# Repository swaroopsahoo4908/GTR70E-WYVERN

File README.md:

# GTR70E WYVERN — fin-controlled research rocket

Authors: Swaroop Sahoo, Chris Liu, Allison Hong

A single-stage, 58 mm, actively stabilised rocket. Four servo-driven triangular fins sit in one ring just above the motor, all at the same station, and steer it on ascent; four fixed rectangular stabilizers run the length of the motor and keep it passively stable. The motor's ejection gas reaches the recovery bay through a printed PC-FR tube on the centreline, and the avionics ride on a square spine around that tube. The flight computer is a Raspberry Pi Pico 2 W (radio left off) that logs everything to an Adafruit 4682 microSD; there is no radio, and a pushbutton through the wall arms it on the pad. The thrust-vector-control revision lives, complete, in `TVC ARCHIVED/`.

## Key numbers (`Documentation/CANONICAL_NUMBERS.md` is the full, generated list)

| | |
|---|---|
| Length / OD | 693 mm / 58 mm, four printed sections (each fits a 256 mm printer), only the nose separates |
| Liftoff mass | 784.5 g on an AeroTech Econojet F42-4T (T/W 4.7 avg; 4 motors $98.98 at eRockets, no certification) |
| CG / CP / margin | 338 / 422 mm, 1.44 cal at liftoff, 1.63 at burnout; 253 g nose ballast, stabilizers 81 x 20 mm at 45°, H45 flight fins |
| Rail exit | 15.0 m/s off the 6 ft Estes Pro Series II rail (printed 1010 buttons) |
| Apogee | 176 m (577 ft, under the 600 ft cap) at 6.3 s; motor ejection (4 s delay) via the central printed PC-FR bypass tube |
| Control | 4 x EMAX ES9251 II in one ring on their own 5 V rail (rev 3f; was the KST X08 Plus), bases 5 mm from the axis, ±15°, q-scheduled PID at 200 Hz; gust case 0.6° RMS tilt vs 10.8° with fins locked; fins active from rail exit until q̄ < 15 Pa (96 % of the ascent); in-flight authority manoeuvre (doublets + 1° steps) |
| Avionics | Raspberry Pi Pico 2 W (rev 4b, radio off) logging to an Adafruit 4682 microSD; BNO085 on one I2C bus, BMP388 + BME688 on the other, on a square spine around the bypass tube; arm button + LED in the -Y wall |
| Power | 2S 450 mAh through a Pololu 2810 MOSFET switch flipped through a wall slot; 26-min mission uses 35 mAh (6.9x margin) |
| Data | 96 B records at 100 Hz to the card once armed, manoeuvre summary in `MANxxx.TXT`; USB CSV at 10 Hz on the bench and pad only; no telemetry in flight |

## Research questions (`Documentation/Research_Plan.md`)

Main question: how do aerofoil section (flat plate, 6 % double wedge, NACA 0006, NACA 0012) and fin height (20-40 mm) set the control authority of a servo-actuated triangular fin, and which combination gives the most? Tunnel Phase A (one fin on a reflection plane) plus simulation.

- SQ1: how much do the rectangular stabilizers reduce installed authority, as a function of span and azimuth? `wf_stabilizer.py` plus tunnel Phase B (full finset, stabilizers off / 30 / 40 mm).
- SQ2: how well do the simulations predict the tunnel, and how far does that carry to flight? Three launches of the best section at H* - 5, H*, H* + 5.

## Repository

```
GTR70E WYVERN/
├── README.md
├── Documentation/
│   ├── Design_Overview.md          architecture, servo ring, spine, stability/ballast, motor, bypass sizing
│   ├── Research_Plan.md            main RQ + SQ1/SQ2, single fin vs four, test matrix, selection rule
│   ├── Wind_Tunnel_Adaptation.md   Phase A half-model (stock section), Phase B 200 x 200 x 750 + stabilizer tail
│   ├── Electronics_Telemetry.md    board choice, pin map, power + battery budget, arming, logging, firmware
│   ├── Build_and_Test.md           print settings, assembly stages, sign check, ejection test, pad procedure
│   ├── Decisions_and_Risks.md      decision log + risk register
│   ├── CANONICAL_NUMBERS.md        generated by gen_canonical_md.py
│   ├── WYVERN_BOM.xlsx             built by build_bom.py: one sheet, Rocket / Wind Tunnel / Flow-Vis, everything to buy
│   └── diagrams/                   D0 renders, D1 layout, D2 sections, D3 assembly, D4 tunnel, D5 research plan, D6 fit check
├── 3D parts/
│   ├── _generator/                 gen_wyvern_fin.py (CadQuery), gen_fit_assembly.py (fit check), mass_report.json
│   ├── vendor/                     Adafruit + Pololu STEP models of the bought boards
│   ├── flight/                     STEP + STL for every printed flight part
│   ├── control_fins/<profile>/     4 profiles x H20-45
│   ├── wind_tunnel/                WTA_* Phase A panel/cradle/transition, WTB_* stabilizer tail + blades, WT_* Phase B
│   └── assembly/                   full assembly STEP + STL, fit-check assembly + FIT_REPORT.md
├── Simulations/
│   ├── wf_core.py                  single source of truth (geometry, masses, motors, aero, spine board layout)
│   ├── motors/                     RASP .eng curves from thrustcurve.org (F67W, F67C, G74W, F50T, G40W)
│   ├── wf_flightsim.py             3-DOF closed-loop flight sim + motor trade + gain tuning + authority manoeuvre
│   ├── wf_fin_authority.py         4 x 8 profile/height authority sweep (main RQ)
│   ├── wf_stabilizer.py            stabilizer span x azimuth sweep (SQ1)
│   ├── wf_stabilizer_planform_trade.py  equal-span / AIM-54 layout trade (S4 plot)
│   ├── wf_apogee_cap_trade.py      rev 3d: 600 ft cap without losing authority (C plot)
│   ├── wf_motor_study.py           F42-4T vs F27R-4 / F20W-4 / F20W-7 on 6-10 ft rails (D plot)
│   ├── wf_bypass.py · wf_power.py
│   ├── wyvern_finsim/              GUI simulation & dataset suite (run_gui.py), headless datagen.py
│   └── CFD/                        vortex-panel 2D + vlm.py 3D vortex lattice + simscale/ RANS package (10 cases)
├── Flight Computer/
│   ├── firmware/wyvern_fin/        flight firmware (Pico 2 W, arduino-pico, compiles) + sil_host/
│   ├── host/                       wyvern_host.py: SD log decoder, USB live plot
│   ├── test_code/                  t1 I2C scan, t2 servo cal + bench sign check, t3 arm button + SD soak
│   └── wiring/                     gen_wiring.py -> W1 wiring, W2 power tree, W3 system, W4 spine + perfboard
├── Wind Tunnel/                    Jerrod H STLs (unchanged) + wt_balance_daq (Metro M4: servo + 2 x HX711 balance + BME688)
├── Data/                           Flight / Motor / Wind Tunnel (empty until testing)
├── Paper/
└── TVC ARCHIVED/                   everything from the TVC revision that is not reused
```

## Re-running the cascade

```bash
pip install cadquery numpy-stl matplotlib openpyxl
cd "3D parts/_generator" && python3 gen_wyvern_fin.py          # CAD + mass_report.json (~25 s)
python3 gen_fit_assembly.py                                     # fit check with vendor models (~2 min)
cd ../../Simulations
python3 wf_core.py --report                                    # canonical_numbers.json
python3 CFD/run_airfoil_cfd.py && python3 CFD/vlm.py
python3 wf_flightsim.py            # add --retune after any mass/geometry change
python3 wf_fin_authority.py        # ~1 min
python3 wf_stabilizer.py           # ~20 s
python3 wf_stabilizer_planform_trade.py
python3 wf_apogee_cap_trade.py && python3 wf_motor_study.py
python3 wf_bypass.py && python3 wf_power.py
cd ../Documentation && python3 gen_canonical_md.py && python3 build_bom.py
cd diagrams && python3 gen_vehicle_drawings.py && python3 gen_cad_renders.py && python3 gen_tunnel_research.py && python3 gen_fit_render.py
cd "../../Flight Computer/wiring" && python3 gen_wiring.py
```

Then re-run `python3 "Flight Computer/firmware/sil_host/sil_check.py"` (firmware vs sim manoeuvre metrics) and `python3 Simulations/CFD/simscale/gen_simscale.py` if the geometry changed. Copy any changed gains or limits into `Flight Computer/firmware/wyvern_fin/fc_config.h` and run `python3 sync_headers.py`.

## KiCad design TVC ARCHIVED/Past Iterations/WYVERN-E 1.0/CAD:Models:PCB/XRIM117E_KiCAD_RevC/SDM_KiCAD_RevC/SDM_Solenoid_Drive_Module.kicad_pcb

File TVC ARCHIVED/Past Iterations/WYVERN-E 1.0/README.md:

# WYVERN-E 1.0

An experimental 70/127 mm research rocket demonstrating jet-vane thrust-vector control and a
custom avionics stack, serving as the first hardware PDR for the XRIM-117 WYVERN concept.

A Skylight Rocketry venture. Architecture revision PDR-004. *Superseded by WYVERN-E 2.0
(open-source solenoid TVC + custom RP2350B two-board PCB).*

---

## Overview

WYVERN-E 1.0 established the physical design envelope — two body diameter candidates (70 mm PDR-002
and 127 mm PDR-003/004), a jet-vane TVC geometry, the wind tunnel test infrastructure, and the
first KiCad avionics layout (XRIM117 RevB/C and XRIM117E). The program reached PDR-004 full
assembly before being superseded by the cleaner open-source two-board architecture of 2.0.

---

## Folder structure

```
WYVERN-E 1.0/
├── README.md                          ← this file
├── CAD:Models:PCB/                    ← OpenRocket sims, STL parts, KiCad PCBs, SVG schematics
│   ├── XRIM117_PTD_PDR002_70mm.ork    ← 70 mm PDR-002 baseline sim
│   ├── XRIM117E_PDR003_127mm.ork      ← 127 mm PDR-003 sim
│   ├── XRIM117E_PDR003_127mm_F15.ork  ← 127 mm F15-motor variant
│   ├── XRIM117E_PDR003_127mm_FLIGHT.ork
│   ├── XRIM117E_PDR004_FULL.ork       ← PDR-004 full assembly sim
│   ├── XRIM117E_PDR004_TVC_ONLY.ork   ← PDR-004 TVC-only stage sim
│   ├── XRIM117_all_parts/             ← 19-part STL library (nose, tubes, fins, gimbal, motor mount…)
│   ├── XRIM117E_KiCAD_RevC/           ← XRIM117E avionics KiCad RevC
│   ├── XRIM117_KiCAD_RevB/            ← XRIM117 avionics KiCad RevB
│   ├── XRIM117_EasyEDA_v3/            ← EasyEDA schematic source (pre-KiCad migration)
│   ├── xrim117_avionics_v4.svg        ← avionics schematic (SVG)
│   ├── xrim117_jetavane_tvc.svg       ← jet-vane TVC diagram (SVG)
│   ├── XRIM117_PCB_Layouts.html       ← rendered PCB layout view
│   ├── WYVERN_Engineering_Analysis.pdf ← structural and aero analysis
│   └── WYVERN_Simulator.md            ← flight simulation environment notes
├── Wind Tunnel/                       ← wind tunnel design, BOM, and test data
│   ├── Wind Tunnel Build.md           ← construction and instrumentation notes
│   ├── wind_tunnel_bom.xlsx           ← wind tunnel bill of materials
│   ├── WYVERN_wind_tunnel_spec.html   ← tunnel specification (HTML)
│   ├── WindTunnel_all_parts/          ← 14-part STL assembly (bellmouth, settling chamber,
│   │                                     contraction cone ×6, test section ×3, diffuser, fan)
│   └── WYVERN_WindTunnel_v2.zip       ← full tunnel archive
├── Docs:Decks/                        ← presentations and technical overview documents
│   ├── XRIM117_WYVERN_PitchDeck.pptx ← investor/competition pitch deck
│   ├── XRIM117_WYVERN_TechOverview.docx ← technical overview document
│   ├── XRIM117_PTD_PDR002_RevA_70mm.docx ← PDR-002 preliminary design review
│   └── XRIM117_NDA.docx               ← NDA (superseded by WYVERN/WYVERN NDA.md)
└── _OLD FILES/                        ← superseded PCB revisions (kept for reference)
    └── PCB/FCM_KiCAD/                 ← earlier KiCad layout with gerbers
```

---

## Key design parameters (PDR-004)

| Parameter | Value |
|---|---|
| Body diameters evaluated | 70 mm (PDR-002), 127 mm (PDR-003/004) |
| TVC method | Jet-vane (carbon-composite vanes in motor exhaust) |
| Avionics | Custom KiCad PCB — XRIM117 RevB → XRIM117E RevC |
| Wind tunnel | Open-return, 14-part 3D-printed, bellmouth inlet |
| Simulation | OpenRocket + custom Python flight simulator |

---

## Related

- `../WYVERN-E 2.0/` — successor: open-source solenoid TVC + RP2350B two-board PCB
- `../WYVERN/` — XRIM-117 concept and doctrine documents
- [[WYVERN MOC]] — Obsidian index

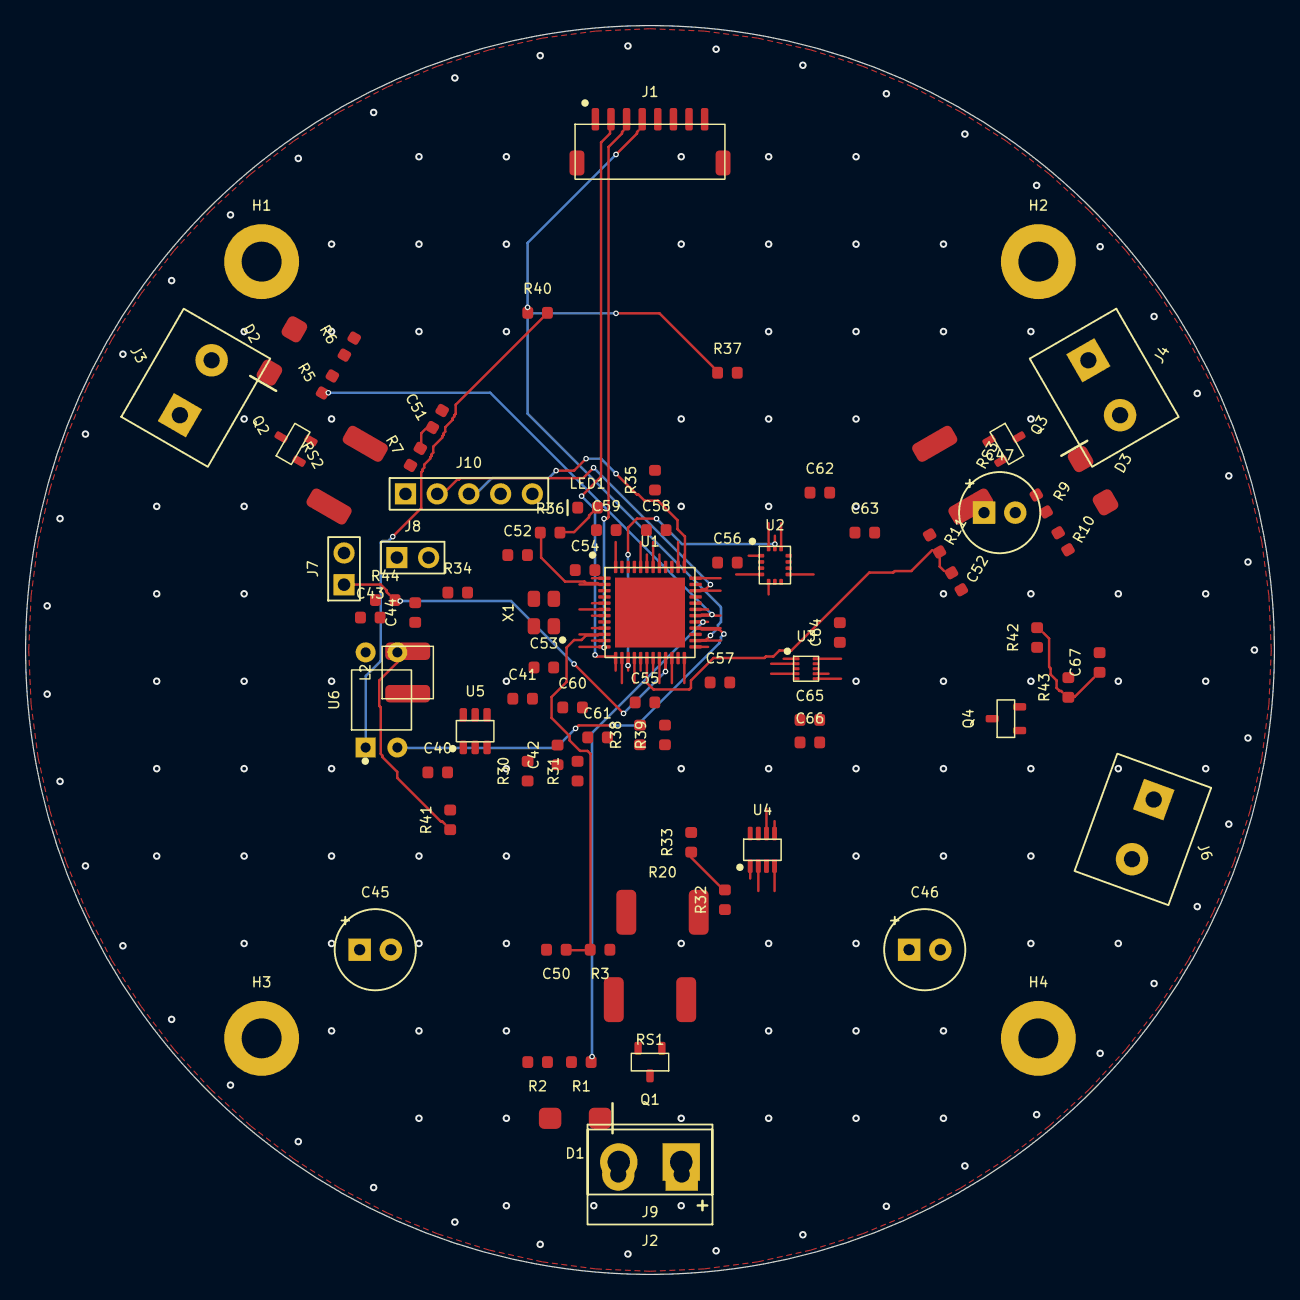
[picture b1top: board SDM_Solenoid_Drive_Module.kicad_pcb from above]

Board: 2 copper layers, 100.0 x 100.0 mm, 84 parts (0 on the bottom side), 50 nets.

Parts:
C40, C50, C51, C52, C54, C56, C57, C58, C60, C62, C65, C66: 100nF; C_0603
C41, C42: 10uF 25V; C_0603
C43, C44: 22uF; C_0603
C45, C46, C47: 470uF; CP_Radial_D6.3mm_P2.50mm
C52#2, C53: 18pF; C_0603
C55: 4.7uF; C_0603
C59: 10uF; C_0603
C61: 1uF; C_0603
C63: 2.2uF; C_0603
C64, C67: 10nF; C_0603
D1, D2, D3: SS34; D_SMA
H1, H2, H3, H4: M3; MountingHole_M3
J1: to CCM; JST_GH_SM08B-GHS-TB
J2: SOL1; TerminalBlock_2P_5.08mm
J3: SOL2; TerminalBlock_2P_5.08mm
J4: SOL3; TerminalBlock_2P_5.08mm
J6: SUSTAIN; TerminalBlock_2P_5.08mm
J7: REED; PinHeader_1x02_P2.54mm
J8: BOOT0; PinHeader_1x02_P2.54mm
J9: XT30 2S; XT30_Male_Vertical
J10: SWD; PinHeader_1x05_P2.54mm
L2: 10uH; L_4x4mm
LED1: STAT; LED_0603
Q1, Q2, Q3, Q4: AO3400A; SOT-23
R1, R5, R9: 100R; R_0603
R2, R6, R10, R32, R37, R41, R42: 100k; R_0603
R3, R7, R11, R36: 1k; R_0603
R20: 10m 2512; R_2512_Shunt
R30: 45.3k; R_0603
R31, R34, R35, R44: 10k; R_0603
R33, R43: 27k; R_0603
R38, R39: 4.7k; R_0603
R40: 330R; R_0603
RS1, RS2, RS3: 20m 2512; R_2512_Shunt
U1: STM32F411CEU6; UFQFPN-48_7x7mm_P0.5mm
U2: ICM-42688-P; ICM-42688-P_LGA-14_2.5x3mm
U3: BMP388; BMP388_LGA-10_2x2mm
U4: INA219; SOT-23-8
U5: TPS54202; SOT-23-6
U6: PC817; PC817_DIP-4
X1: 8MHz; Crystal_3225_4Pin

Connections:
+3V3: C43.1, C44.1, C56.1, C57.1, C58.1, C59.1, C60.1, C61.1, C62.1, C63.1, C64.1, C65.1, C66.1, J8.2, J10.1, L2.2, R30.1, R38.1, R39.1, R44.1, U1.1, U1.9, U1.24, U1.36, U1.48, U2.5, U2.8, U3.1, U3.6, U3.10, U4.4
ARM_IN: J1.4, R37.1, R40.1, U1.26
ARM_IN_R: R40.2, U6.1
BMP_INT: U1.41, U3.7
BOOT0: J8.1, R34.1, U1.44
BUCK_BOOT: C40.1, U5.6
BUCK_FB: R30.2, R31.1, U5.4
BUCK_SW: C40.2, L2.1, U5.2
GND: C41.2, C42.2, C43.2, C44.2, C45.2, C46.2, C47.2, C50.2, C51.2, C52.2, C52#2.2, C53.2, C54.2, C55.2, C56.2, C57.2, C58.2, C59.2, C60.2, C61.2, C62.2, C63.2, C64.2, C65.2, C66.2, C67.2, J1.1, J1.7, J1.8, J1.MP1, J1.MP2, J7.2, J9.2, J10.5, LED1.1, Q4.2, R2.2, R6.2, R10.2, R31.2, R33.2, R34.2, R35.2, R37.2, R41.2, R43.2, RS1.2, RS2.2, RS3.2, U1.8, U1.23, U1.35, U1.47, U1.49, U2.6, U2.7, U2.9, U3.3, U3.5, U3.8, U3.9, U4.3, U4.7, U4.8, U5.1, X1.2, X1.4
I2C1_SCL: R39.2, U1.42, U3.2, U4.5
I2C1_SDA: R38.2, U1.43, U3.4, U4.6
IMU_CS: U1.25, U2.12
IMU_INT1: U1.38, U2.4
LED_R: LED1.2, R36.2
LED_STATUS: R36.1, U1.2
NRST: C54.1, J10.4, U1.7
PB2_STRAP: R35.1, U1.20
REED: J7.1, R44.2, U1.21
SOL1_D: D1.1, J2.2, Q1.3
SOL1_G: Q1.1, R1.2, R2.1
SOL1_PWM: R1.1, U1.29
SOL1_SH: Q1.2, R3.1, RS1.1
SOL1_SNS: C50.1, R3.2, U1.10
SOL2_D: D2.1, J3.2, Q2.3
SOL2_G: Q2.1, R5.2, R6.1
SOL2_PWM: R5.1, U1.30
SOL2_SH: Q2.2, R7.1, RS2.1
SOL2_SNS: C51.1, R7.2, U1.11
SOL3_D: D3.1, J4.2, Q3.3
SOL3_G: Q3.1, R9.2, R10.1
SOL3_PWM: R9.1, U1.31
SOL3_SH: Q3.2, R11.1, RS3.1
SOL3_SNS: C52.1, R11.2, U1.18
SPI1_MISO: U1.16, U2.1
SPI1_MOSI: U1.17, U2.14
SPI1_SCK: U1.15, U2.13
SUS_CONT: C67.1, R42.2, R43.1, U1.14
SUS_D: J6.2, Q4.3, R42.1
SUS_FIRE: U1.28, U6.2
SUS_GATE: Q4.1, R41.1, U6.3
SWCLK: J10.3, U1.37
SWDIO: J10.2, U1.34
UART_RX: J1.2, U1.13
UART_TX: J1.3, U1.12
VBAT2S: C41.1, C42.1, J6.1, J9.1, R20.1, R32.1, U4.1, U5.3, U6.4
VBAT_SENSE: R32.2, R33.1, U1.19
VCAP: C55.1, U1.22
V_SOL: C45.1, C46.1, C47.1, D1.2, D2.2, D3.2, J2.1, J3.1, J4.1, R20.2, U4.2
XIN: C52#2.1, U1.5, X1.1
XOUT: C53.1, U1.6, X1.3

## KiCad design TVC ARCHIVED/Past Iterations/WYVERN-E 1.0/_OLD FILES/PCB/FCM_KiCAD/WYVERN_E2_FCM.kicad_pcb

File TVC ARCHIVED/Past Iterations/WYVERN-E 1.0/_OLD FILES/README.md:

# _OLD FILES — archived, superseded material

Moved out of `WYVERN-E 2.0/` on 2026-06-18. Nothing here is needed for the current
(two-board) iteration; kept only for reference/history. Original folder structure is
preserved, so any item can be moved straight back to where it came from.

## What's here

*Superseded single-board PCB design* (`WYVERN_E2_FCM.*`) — the original one-board flight
computer, replaced by the two-board split (`WYVERN_E2_B1` + `WYVERN_E2_B2`):
- `PCB/FCM_KiCAD/WYVERN_E2_FCM.kicad_pcb/.sch/.pro/.prl`, `_placement.png`
- `PCB/FCM_KiCAD/gerbers/WYVERN_E2_FCM*` (gerbers, BOM, CPL, zip)
- `PCB/WYVERN_E2_FCM_PCB_Documentation.md`, `PCB/WYVERN_E2_FCM_HANDOFF_BRIEF.md`

*Build cruft / checkpoints / backups*:
- `*_route.pkl`, `route_state.pkl` (autorouter checkpoints), `DRC.rpt`
- `gen_fcm.py.bak`, `gen_fcm.py.bak2`
- `.history/` (editor local-history git), temp files, `__pycache__/`, `.DS_Store`

## Note
`gen_fcm.py` itself was NOT archived — it is still imported by the current build
(`project_file` and helpers), so it remains in `PCB/generator/`.

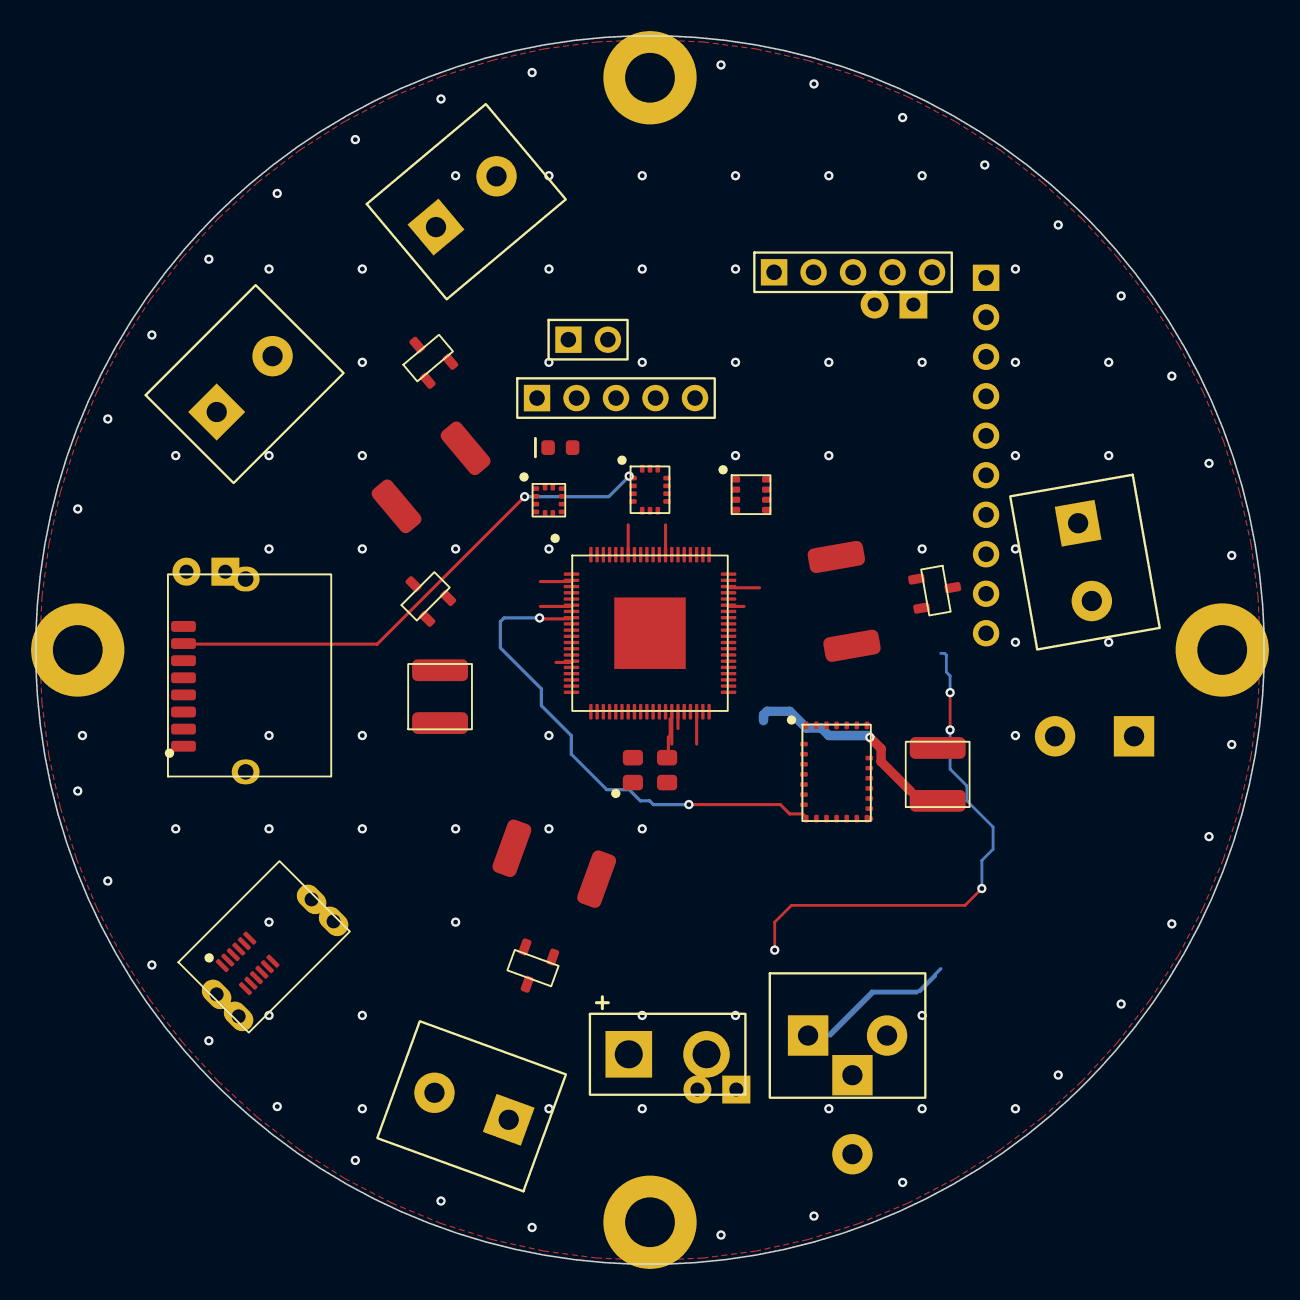
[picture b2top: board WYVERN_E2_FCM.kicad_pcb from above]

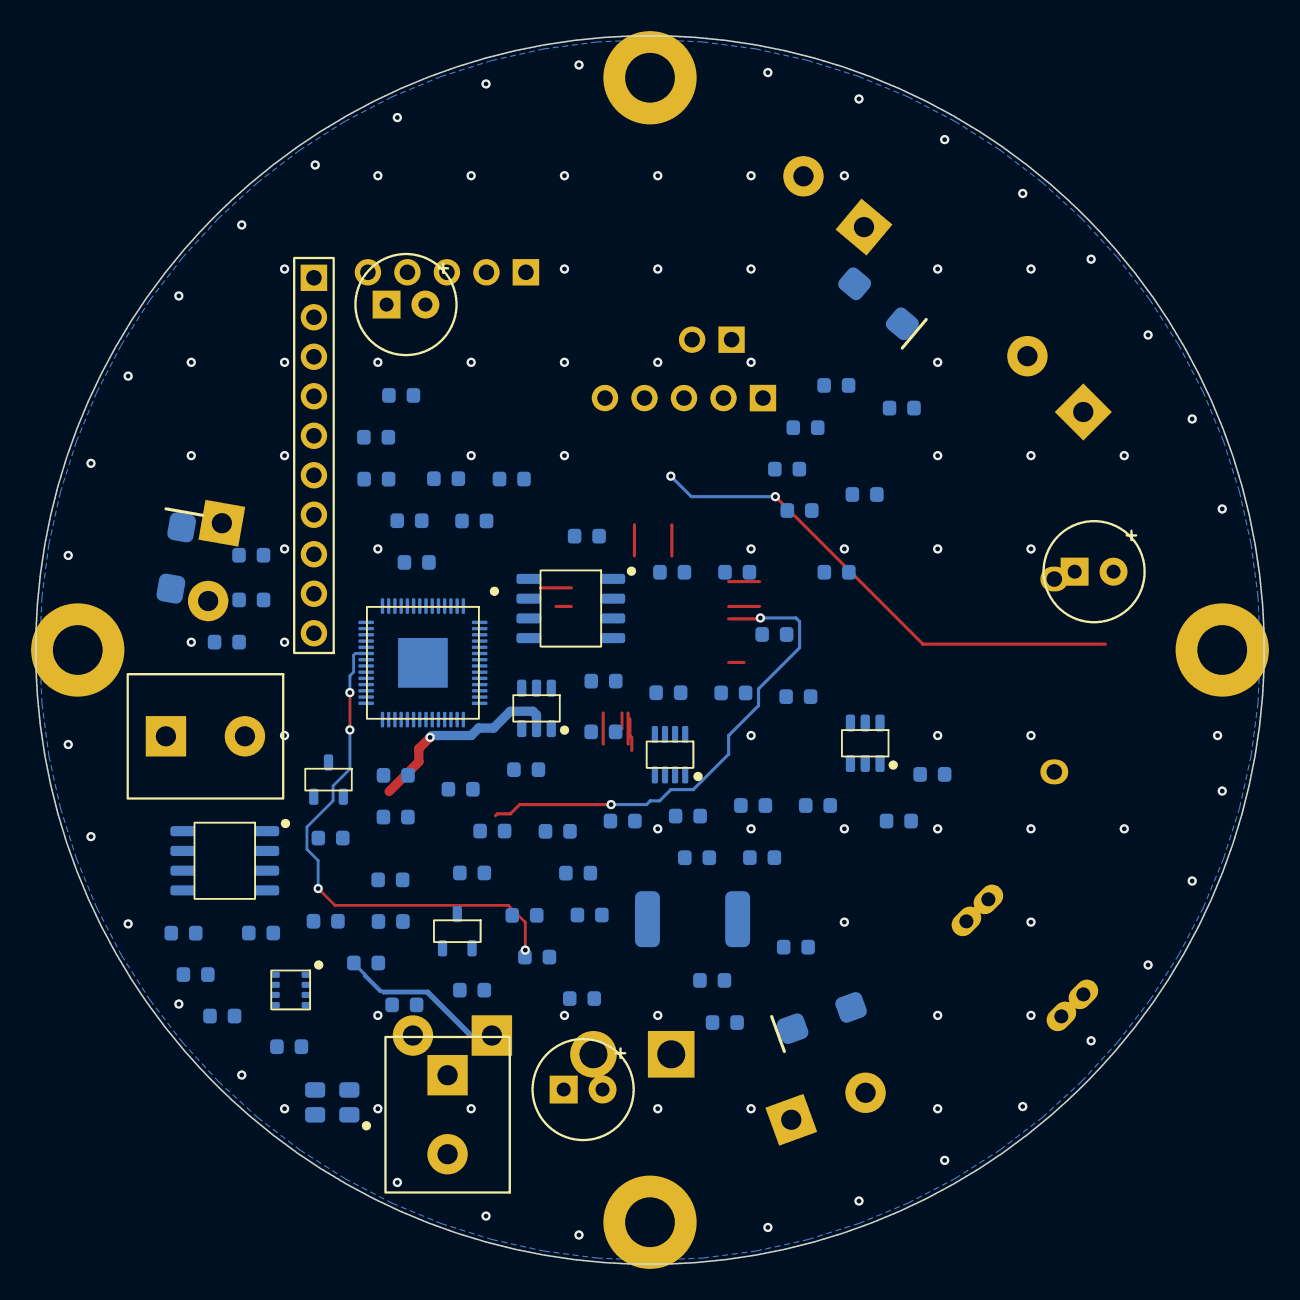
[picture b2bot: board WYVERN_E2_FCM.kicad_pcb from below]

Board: 4 copper layers, 79.0 x 79.0 mm, 113 parts (82 on the bottom side), 81 nets.

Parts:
C1, C2, C71, C72: 18pF; C_0603
C3, C10, C11, C12, C13, C14, C15, C16, C17, C20, C40, C41, C42, C70, C74, C75, C76, C77, C78, C79, C80: 100nF; C_0603
C30, C31, C32: 470uF; CP_Radial_D6.3mm_P2.50mm
C50, C73: 1uF; C_0603
D1, D2, D3: SS34; D_SMA
H1, H2, H3, H4: M3; MountingHole_M3
J1: SWD; PinHeader_1x05_P2.54mm
J2: USB-C; USB-C_Receptacle_2.0
J3: microSD; microSD_Push_Molex
J4: BNO055; PinHeader_1x10_P2.54mm
J5: VIBE; TerminalBlock_2P_5.08mm
J6: 12V NiCd; XT30_Male_Vertical
J7: SOL1; TerminalBlock_2P_5.08mm
J8: SOL2; TerminalBlock_2P_5.08mm
J9: SOL3; TerminalBlock_2P_5.08mm
J11: 2ND IGN; TerminalBlock_2P_5.08mm
J12: REED; PinHeader_1x02_P2.54mm
J14: DROGUE PYRO; TerminalBlock_2P_5.08mm
J15: MAIN PYRO; TerminalBlock_2P_5.08mm
J16: DEPLOY SWD; PinHeader_1x05_P2.54mm
L1, L2: 10uH; L_4x4mm
LED1: STAT; LED_0603
Q1, Q2, Q3, Q4, Q5, Q6: AO3400A; SOT-23
R1, R9, R11, R44, R60: 10k; R_0603
R2, R3: 5.1k; R_0603
R4, R5, R61, R62: 4.7k; R_0603
R6: 1M; R_0603
R7: 10m; R_2512_Shunt
R8: 45.3k; R_0603
R10: 73.2k; R_0603
R12, R21, R25, R29, R40, R41, R45, R46, R47, R49: 100k; R_0603
R13, R42, R48, R50: 18k; R_0603
R20, R24, R28: 100R; R_0603
R22, R26, R30, R43: 1k; R_0603
RS1, RS2, RS3: 20m; R_2512_Shunt
U1: RP2350B; QFN-80-1EP_10x10mm_P0.4mm
U2, U11: W25Q32JV; SOIC-8_3.9x4.9mm_P1.27mm
U4: ICM-42688-P; ICM-42688-P_LGA-14_2.5x3mm
U5, U12: BMP280; BME280_LGA-8_2.5x2.5mm
U6: LIS3MDL; LIS3MDL_LGA-12_2x2mm
U7: INA219; SOT-23-8
U8: TPS54202_3V3; SOT-23-6
U9: TPS54202_5V; SOT-23-6
U10: RP2040; QFN-56-1EP_7x7mm_P0.4mm
U13: BNO055; BNO055_LGA-28_3.8x5.2mm
X1, X2: 12MHz; Crystal_3225_4Pin

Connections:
+1V1: C50.1, C73.1, U1.18, U1.20, U1.60, U10.23, U10.45, U10.50
+3V3: C3.1, C10.1, C11.1, C12.1, C13.1, C14.1, C15.1, C16.1, C17.1, C20.1, C70.1, C74.1, C75.1, C76.1, C77.1, C78.1, C79.1, C80.1, J1.1, J3.4, J4.1, J4.2, J16.1, L1.2, R1.1, R4.1, R5.1, R8.1, R44.1, R60.1, R61.1, R62.1, U1.1, U1.11, U1.19, U1.21, U1.31, U1.39, U1.40, U1.41, U1.51, U1.61, U1.69, U1.70, U1.71, U1.78, U1.79, U1.80, U2.8, U4.5, U4.8, U5.1, U5.4, U5.6, U6.1, U6.5, U6.12, U7.4, U10.1, U10.10, U10.22, U10.33, U10.42, U10.43, U10.44, U10.48, U10.49, U11.8, U12.1, U12.4, U12.6, U13.1, U13.5, U13.13, U13.19, U13.26
+5V: L2.2, R10.1
BK3_FB: R8.2, R9.1, U8.4
BK3_SW: L1.1, U8.2
BK5_FB: R10.2, R11.1, U9.4
BK5_SW: L2.1, U9.2
BNO_INT: J4.7, U1.56
BNO_O_INT: U1.8, U13.8
CC1: J2.3, R2.1
CC2: J2.4, R3.1
DEP_ARM: U1.6, U10.7
DEP_I2C_SCL: R62.2, U10.12, U12.7
DEP_I2C_SDA: R61.2, U10.11, U12.3
DEP_QSPI_SCLK: U10.52, U11.6
DEP_QSPI_SD0: U10.53, U11.5
DEP_QSPI_SD1: U10.55, U11.2
DEP_QSPI_SD2: U10.54, U11.3
DEP_QSPI_SD3: U10.51, U11.7
DEP_QSPI_SS: U10.56, U11.1
DEP_RUN: J16.4, R60.2, U10.26
DEP_STATUS: U1.7, U10.9
DEP_SWCLK: J16.3, U10.24
DEP_SWD: J16.2, U10.25
DEP_UART_RX: U1.5, U10.3
DEP_UART_TX: U1.4, U10.2
DEP_XIN: C71.1, U10.20, X2.1
DEP_XOUT: C72.1, U10.21, X2.3
GND: C1.2, C2.2, C3.2, C10.2, C11.2, C12.2, C13.2, C14.2, C15.2, C16.2, C17.2, C20.2, C30.2, C31.2, C32.2, C40.2, C41.2, C42.2, C50.2, C70.2, C71.2, C72.2, C73.2, C74.2, C75.2, C76.2, C77.2, C78.2, C79.2, C80.2, J1.5, J2.2, J3.6, J4.3, J4.8, J4.9, J4.10, J5.2, J6.2, J12.2, J16.5, LED1.1, Q4.2, Q5.2, Q6.2, R2.2, R3.2, R6.2, R9.2, R11.2, R13.2, R21.2, R25.2, R29.2, R40.2, R42.2, R45.2, R46.2, R48.2, R50.2, RS1.2, RS2.2, RS3.2, U1.81, U2.4, U4.6, U4.7, U4.9, U5.2, U5.5, U5.8, U6.2, U6.3, U6.4, U6.8, U6.9, U6.10, U6.11, U7.3, U7.7, U7.8, U8.1, U9.1, U10.19, U10.57, U11.4, U12.2, U12.5, U12.8, U13.2, U13.3, U13.4, U13.9, U13.10, U13.11, U13.12, U13.14, U13.15, U13.16, U13.17, U13.18, U13.20, U13.21, U13.22, U13.23, U13.24, U13.25, U13.27, U13.28, X1.2, X1.4, X2.2, X2.4
I2C0_SCL: J4.5, R5.2, U1.47, U5.7, U6.6, U7.5, U13.6
I2C0_SDA: J4.4, R4.2, U1.46, U5.3, U6.7, U7.6, U13.7
IMU_CS: U1.17, U4.12
IMU_INT1: U1.55, U4.4
LED_R: LED1.2, R43.2
PYRO_DROG_CONT: R47.2, R48.1, U10.39
PYRO_DROG_D: J14.2, Q5.3, R47.1
PYRO_DROG_GATE: Q5.1, R45.1, U10.5
PYRO_IGN_CONT: R41.2, R42.1, U10.38
PYRO_IGN_D: J11.2, Q4.3, R41.1
PYRO_IGN_GATE: Q4.1, R40.1, U10.4
PYRO_MAIN_CONT: R49.2, R50.1, U10.40
PYRO_MAIN_D: J15.2, Q6.3, R49.1
PYRO_MAIN_GATE: Q6.1, R46.1, U10.6
QSPI_SCLK: U1.73, U2.6
QSPI_SD0: U1.74, U2.5
QSPI_SD1: U1.76, U2.2
QSPI_SD2: U1.75, U2.3
QSPI_SD3: U1.72, U2.7
QSPI_SS: U1.77, U2.1
REED: J12.1, R44.2, U1.57
RUN: J1.4, J4.6, R1.2, U1.32
SD_CS: J3.2, U1.23
SOL1_D: D1.1, J7.2, Q1.3
SOL1_G: Q1.1, R20.2, R21.1
SOL1_PWM: R20.1, U1.48
SOL1_SH: Q1.2, R22.1, RS1.1
SOL1_SNS: C40.1, R22.2, U1.59
SOL2_D: D2.1, J8.2, Q2.3
SOL2_G: Q2.1, R24.2, R25.1
SOL2_PWM: R24.1, U1.49
SOL2_SH: Q2.2, R26.1, RS2.1
SOL2_SNS: C41.1, R26.2, U1.62
SOL3_D: D3.1, J9.2, Q3.3
SOL3_G: Q3.1, R28.2, R29.1
SOL3_PWM: R28.1, U1.50
SOL3_SH: Q3.2, R30.1, RS3.1
SOL3_SNS: C42.1, R30.2, U1.63
SPI1_MISO: J3.7, U1.15, U4.1
SPI1_MOSI: J3.3, U1.14, U4.14
SPI1_SCK: J3.5, U1.13, U4.13
STATUS_LED: R43.1, U1.54
SWCLK: J1.3, U1.35
SWDIO: J1.2, U1.36
USB_DM: J2.6, U1.38
USB_DP: J2.5, U1.37
VBAT12: J6.1, J11.1, J14.1, J15.1, R7.1, R12.1, U7.1, U8.3, U9.3
VBAT_SENSE: R12.2, R13.1, U1.64
VIBE_SNS: J5.1, R6.1, U1.68
V_SOL: C30.1, C31.1, C32.1, D1.2, D2.2, D3.2, J7.1, J8.1, J9.1, R7.2, U7.2
XIN: C1.1, U1.33, X1.1
XOUT: C2.1, U1.34, X1.3

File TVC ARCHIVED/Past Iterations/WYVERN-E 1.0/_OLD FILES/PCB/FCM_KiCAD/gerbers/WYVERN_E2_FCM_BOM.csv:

Comment,Designator,Footprint,Qty,LCSC Part #
100R,"R20,R24,R28",R_0603,3,
100k,"R12,R21,R25,R29,R40,R41,R45,R46,R47,R49",R_0603,10,
100nF,"C10,C11,C12,C13,C14,C15,C16,C17,C20,C3,C40,C41,C42,C70,C74,C75,C76,C77,C78,C79,C80",C_0603,21,
10k,"R1,R11,R44,R60,R9",R_0603,5,
10m,R7,R_2512_Shunt,1,
10uH,"L1,L2",L_4x4mm,2,
12MHz,"X1,X2",Crystal_3225_4Pin,2,
12V NiCd,J6,XT30_Male_Vertical,1,
18k,"R13,R42,R48,R50",R_0603,4,
18pF,"C1,C2,C71,C72",C_0603,4,
1M,R6,R_0603,1,
1k,"R22,R26,R30,R43",R_0603,4,
1uF,"C50,C73",C_0603,2,
20m,"RS1,RS2,RS3",R_2512_Shunt,3,
2ND IGN,J11,TerminalBlock_2P_5.08mm,1,
4.7k,"R4,R5,R61,R62",R_0603,4,
45.3k,R8,R_0603,1,
470uF,"C30,C31,C32",CP_Radial_D6.3mm_P2.50mm,3,
5.1k,"R2,R3",R_0603,2,
73.2k,R10,R_0603,1,
AO3400A,"Q1,Q2,Q3,Q4,Q5,Q6",SOT-23,6,
BMP280,"U12,U5",BME280_LGA-8_2.5x2.5mm,2,
BNO055,U13,BNO055_LGA-28_3.8x5.2mm,1,
BNO055,J4,PinHeader_1x10_P2.54mm,1,
DEPLOY SWD,J16,PinHeader_1x05_P2.54mm,1,
DROGUE PYRO,J14,TerminalBlock_2P_5.08mm,1,
ICM-42688-P,U4,ICM-42688-P_LGA-14_2.5x3mm,1,
INA219,U7,SOT-23-8,1,
LIS3MDL,U6,LIS3MDL_LGA-12_2x2mm,1,
MAIN PYRO,J15,TerminalBlock_2P_5.08mm,1,
REED,J12,PinHeader_1x02_P2.54mm,1,
RP2040,U10,QFN-56-1EP_7x7mm_P0.4mm,1,
RP2350B,U1,QFN-80-1EP_10x10mm_P0.4mm,1,
SOL1,J7,TerminalBlock_2P_5.08mm,1,
SOL2,J8,TerminalBlock_2P_5.08mm,1,
SOL3,J9,TerminalBlock_2P_5.08mm,1,
SS34,"D1,D2,D3",D_SMA,3,
STAT,LED1,LED_0603,1,
SWD,J1,PinHeader_1x05_P2.54mm,1,
TPS54202_3V3,U8,SOT-23-6,1,
TPS54202_5V,U9,SOT-23-6,1,
USB-C,J2,USB-C_Receptacle_2.0,1,
VIBE,J5,TerminalBlock_2P_5.08mm,1,
W25Q32JV,"U11,U2",SOIC-8_3.9x4.9mm_P1.27mm,2,
microSD,J3,microSD_Push_Molex,1,
